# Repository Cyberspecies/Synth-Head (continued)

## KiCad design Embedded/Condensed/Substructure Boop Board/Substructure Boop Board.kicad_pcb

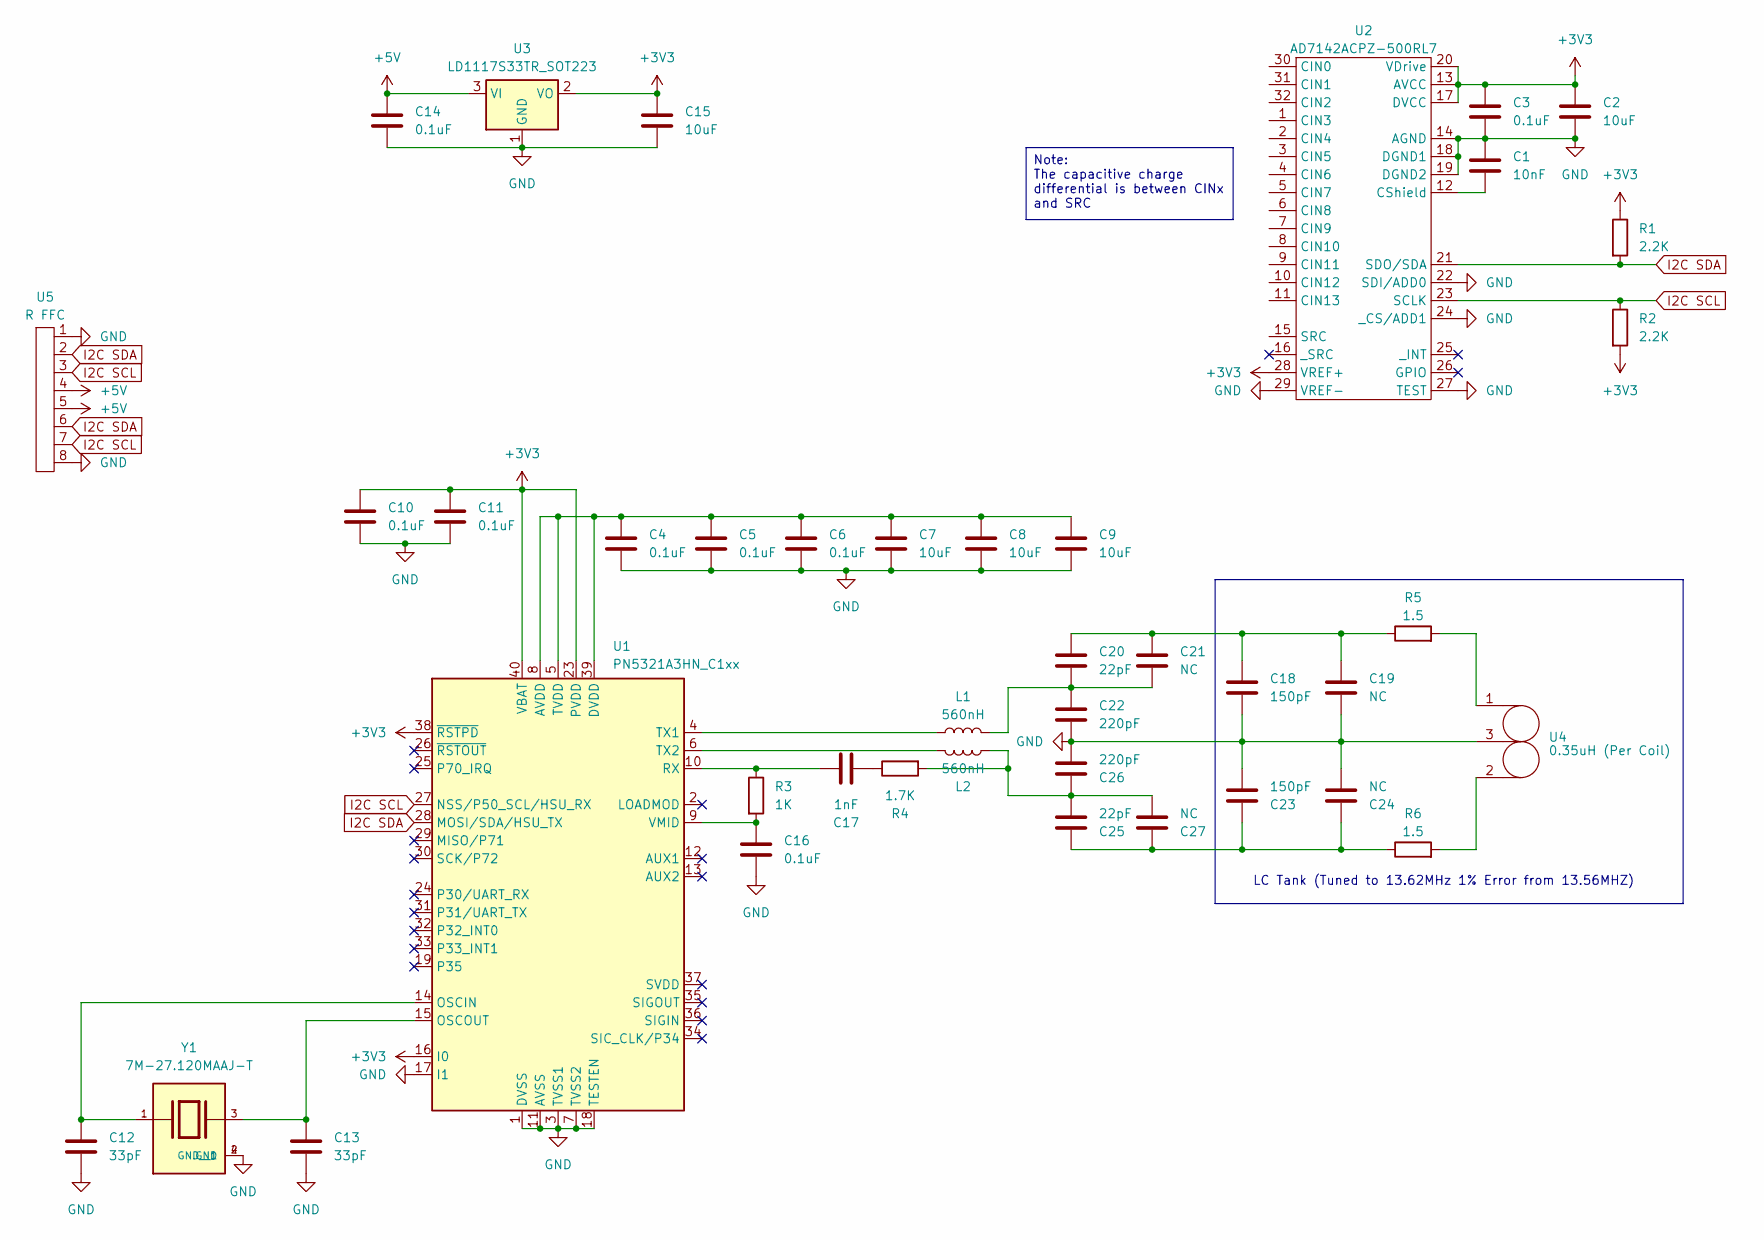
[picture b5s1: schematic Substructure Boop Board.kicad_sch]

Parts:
C1: 10nF; C_0402_1005Metric_Pad0.74x0.62mm_HandSolder; LCSC C327025
C2, C7, C8, C9: 10uF; C_0402_1005Metric_Pad0.74x0.62mm_HandSolder; LCSC C15525
C3, C4, C5, C6, C10, C11, C16: 0.1uF; C_0402_1005Metric_Pad0.74x0.62mm_HandSolder; LCSC C1525
C12, C13: 33pF; C_0402_1005Metric_Pad0.74x0.62mm_HandSolder; LCSC C70465
C14: 0.1uF; C_0603_1608Metric_Pad1.08x0.95mm_HandSolder; LCSC C1591
C15: 10uF; C_0603_1608Metric_Pad1.08x0.95mm_HandSolder; LCSC C3039698
C17: 1nF; C_0402_1005Metric_Pad0.74x0.62mm_HandSolder; LCSC C14442
C18, C23: 150pF; C_0402_1005Metric_Pad0.74x0.62mm_HandSolder; LCSC C86286
C19, C21, C24, C27: NC; C_0402_1005Metric_Pad0.74x0.62mm_HandSolder
C20, C25: 22pF; C_0402_1005Metric_Pad0.74x0.62mm_HandSolder; LCSC C307342
C22, C26: 220pF; C_0402_1005Metric_Pad0.74x0.62mm_HandSolder; LCSC C307445
L1, L2: 560nH; L_0603_1608Metric_Pad1.05x0.95mm_HandSolder; LCSC C502009
R1, R2: 2.2K; C_0402_1005Metric_Pad0.74x0.62mm_HandSolder; LCSC C163447
R3: 1K; C_0402_1005Metric_Pad0.74x0.62mm_HandSolder; LCSC C844716
R4: 1.7K; C_0402_1005Metric_Pad0.74x0.62mm_HandSolder; LCSC C482079
R5, R6: 1.5; C_0402_1005Metric_Pad0.74x0.62mm_HandSolder; LCSC C482091
U1: PN5321A3HN_C1xx; HVQFN-40-1EP_6x6mm_P0.5mm_EP4.1x4.1mm; LCSC C28925
U2: AD7142ACPZ-500RL7; LFCSP-32-1EP_5x5mm_P0.5mm_EP3.1x3.1mm_ThermalVias; LCSC C208139
U3: LD1117S33TR_SOT223; SOT-223-3_TabPin2; LCSC C86781
U4: 0.35uH (Per Coil); 30 x 40 - 2 Pair 2 Layer 2 Turn Loop Antenna
U5: R FFC; FFC 0.8mm 8P
Y1: 7M-27.120MAAJ-T; XTAL_7M-27.120MAAJ-T; PARTREV N/A; DIGIKEY 887-1424-1-ND

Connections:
+3V3: C2.1, C3.1, C10.1, C11.1, C15.1, R1.1, R2.2, U1.16 (I0), U1.23 (PVDD), U1.38 (~RSTPD), U1.40 (VBAT), U2.13 (AVCC), U2.17 (DVCC), U2.20 (VDrive), U2.28 (VREF+), U3.2 (VO)
+5V: C14.1, U3.3 (VI), U5.4, U5.5
GND: C1.1, C2.2, C3.2, C4.2, C5.2, C6.2, C7.2, C8.2, C9.2, C10.2, C11.2, C12.2, C13.2, C14.2, C15.2, C16.2, C18.2, C19.2, C22.2, C23.2, C24.2, C26.1, U1.1 (DVSS), U1.3 (TVSS1), U1.7 (TVSS2), U1.11 (AVSS), U1.17 (I1), U1.18 (TESTEN), U1.41 (AVSS), U2.14 (AGND), U2.18 (DGND1), U2.19 (DGND2), U2.22 (SDI/ADD0), U2.24 (_CS/ADD1), U2.27 (TEST), U2.29 (VREF-), U3.1 (GND), U4.3, U5.1, U5.8, Y1.2 (GND), Y1.4 (GND__1)
I2C SCL: R2.1, U1.27 (NSS/P50_SCL/HSU_RX), U2.23 (SCLK), U5.3, U5.7
I2C SDA: R1.2, U1.28 (MOSI/SDA/HSU_TX), U2.21 (SDO/SDA), U5.2, U5.6
unnamed: C17.2, R4.1
unnamed: C18.1, C19.1, C20.1, C21.1, R5.1
unnamed: C20.2, C21.2, C22.1, L1.2
unnamed: C23.1, C24.1, C25.1, C27.1, R6.1
unnamed: C25.2, C26.2, C27.2, L2.2, R4.2
unnamed: R5.2, U4.1
unnamed: R6.2, U4.2
unnamed: C4.1, C5.1, C6.1, C7.1, C8.1, C9.1, U1.5 (TVDD), U1.8 (AVDD), U1.39 (DVDD)
unnamed: C12.1, U1.14 (OSCIN), Y1.1
unnamed: C13.1, U1.15 (OSCOUT), Y1.3
unnamed: C17.1, R3.1, U1.10 (RX)
unnamed: L1.1, U1.4 (TX1)
unnamed: L2.1, U1.6 (TX2)
unnamed: C16.1, R3.2, U1.9 (VMID)
unnamed: C1.2, U2.12 (CShield)

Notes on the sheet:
LC Tank (Tuned to 13.62MHz 1% Error from 13.56MHZ)
Note: The capacitive charge differential is between CINx and SRC

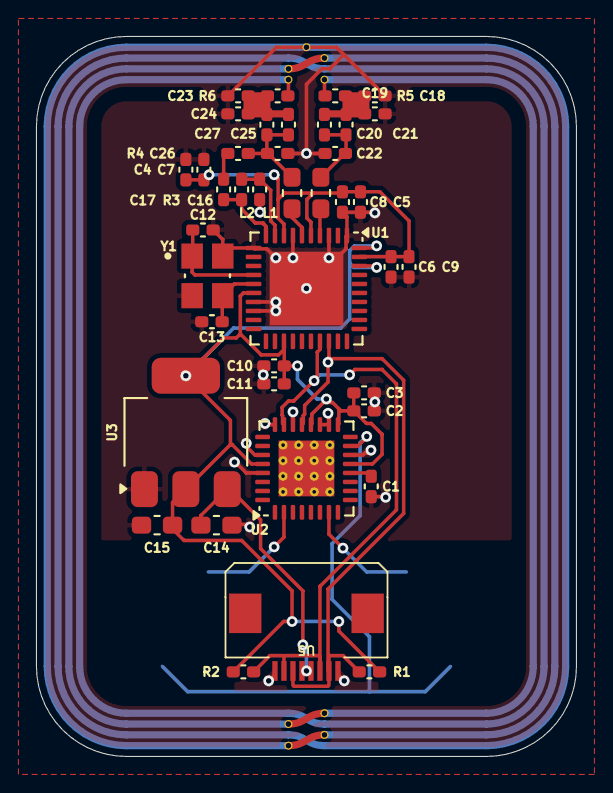
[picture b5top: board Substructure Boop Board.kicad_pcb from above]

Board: 2 copper layers, 30.0 x 40.0 mm, 41 parts (1 on the bottom side), 20 nets.

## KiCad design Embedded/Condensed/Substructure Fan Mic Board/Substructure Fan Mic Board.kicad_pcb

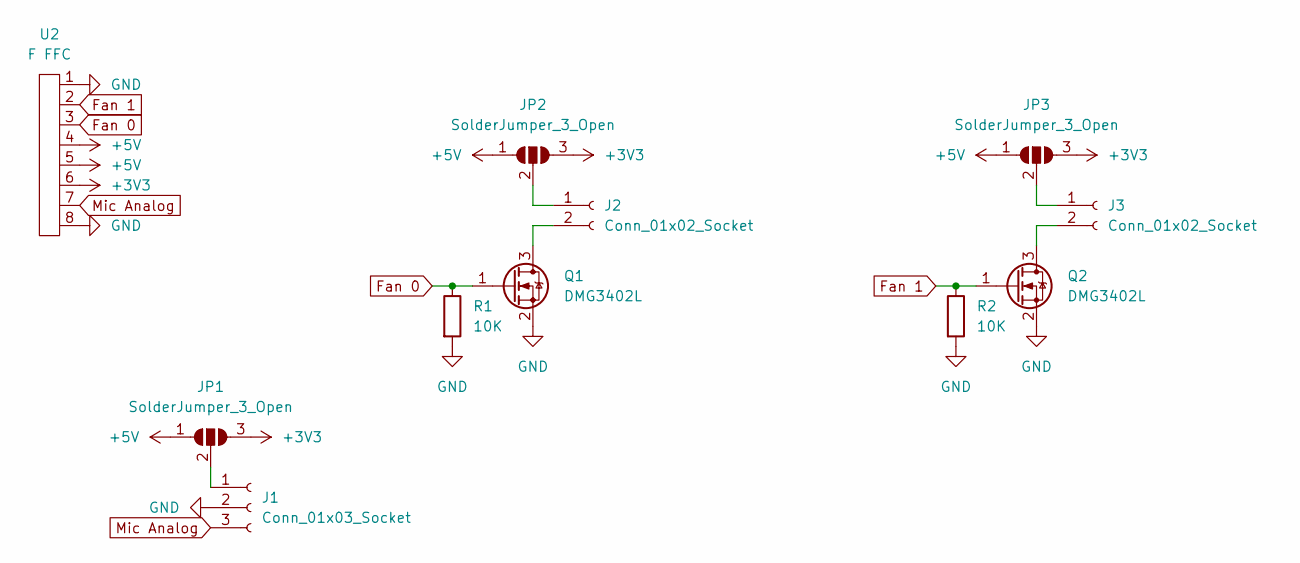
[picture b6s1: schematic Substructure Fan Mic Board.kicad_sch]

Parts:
J1: Conn_01x03_Socket; JST_GH_SM03B-GHS-TB_1x03-1MP_P1.25mm_Horizontal
J2, J3: Conn_01x02_Socket; JST_GH_SM02B-GHS-TB_1x02-1MP_P1.25mm_Horizontal
JP1, JP2, JP3: SolderJumper_3_Open; SolderJumper-3_P1.3mm_Open_RoundedPad1.0x1.5mm
Q1, Q2: DMG3402L; SOT-23; LCSC C96614
R1, R2: 10K; R_0603_1608Metric_Pad0.98x0.95mm_HandSolder; LCSC C98220
U2: F FFC; FFC 0.8mm 8P

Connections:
+3V3: JP1.3 (B), JP2.3 (B), JP3.3 (B), U2.6
+5V: JP1.1 (A), JP2.1 (A), JP3.1 (A), U2.4, U2.5
Fan 0: Q1.1 (G), R1.1, U2.3
Fan 1: Q2.1 (G), R2.1, U2.2
GND: J1.2, Q1.2 (S), Q2.2 (S), R1.2, R2.2, U2.1, U2.8
Mic Analog: J1.3, U2.7
unnamed: J1.1, JP1.2 (C)
unnamed: J2.1, JP2.2 (C)
unnamed: J2.2, Q1.3 (D)
unnamed: J3.1, JP3.2 (C)
unnamed: J3.2, Q2.3 (D)

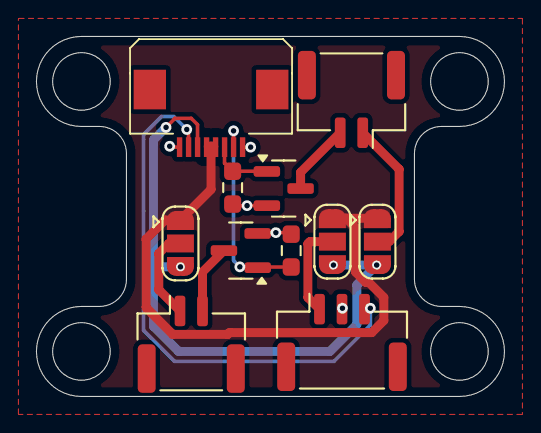
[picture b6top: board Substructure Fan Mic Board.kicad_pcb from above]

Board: 2 copper layers, 26.0 x 20.0 mm, 11 parts (0 on the bottom side), 11 nets.

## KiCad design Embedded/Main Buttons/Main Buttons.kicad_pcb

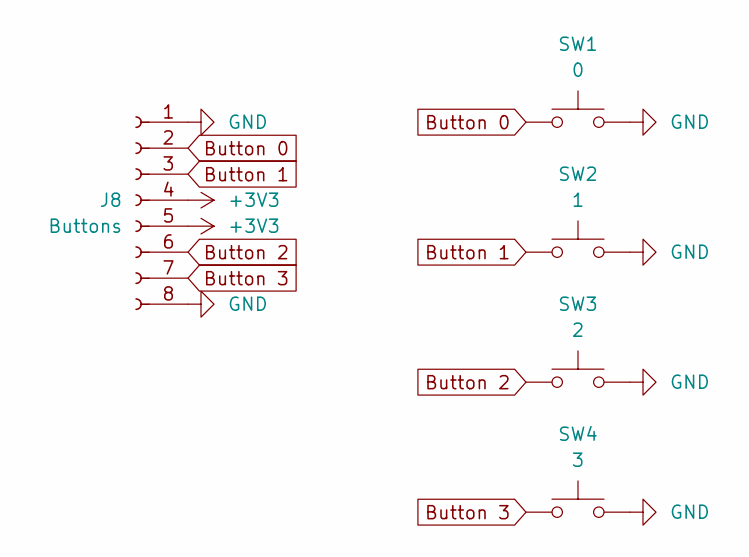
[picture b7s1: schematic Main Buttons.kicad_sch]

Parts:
J8: Buttons; JST_GH_SM08B-GHS-TB_1x08-1MP_P1.25mm_Horizontal
SW1: 0; SW_PUSH_6mm_H5mm
SW2: 1; SW_PUSH_6mm_H5mm
SW3: 2; SW_PUSH_6mm_H5mm
SW4: 3; SW_PUSH_6mm_H5mm

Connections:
+3V3: J8.4, J8.5
Button 0: J8.2, SW1.1
Button 1: J8.3, SW2.1
Button 2: J8.6, SW3.1
Button 3: J8.7, SW4.1
GND: J8.1, J8.8, SW1.2, SW2.2, SW3.2, SW4.2

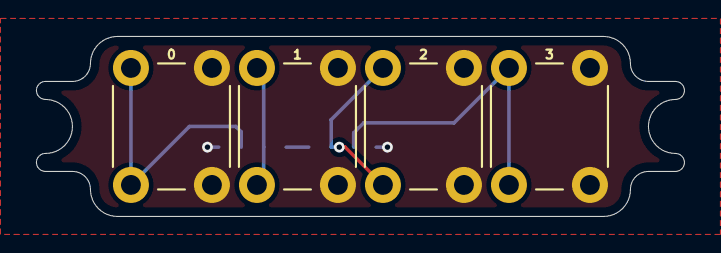
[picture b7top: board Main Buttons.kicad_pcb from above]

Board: 2 copper layers, 36.0 x 10.0 mm, 5 parts (1 on the bottom side), 6 nets.

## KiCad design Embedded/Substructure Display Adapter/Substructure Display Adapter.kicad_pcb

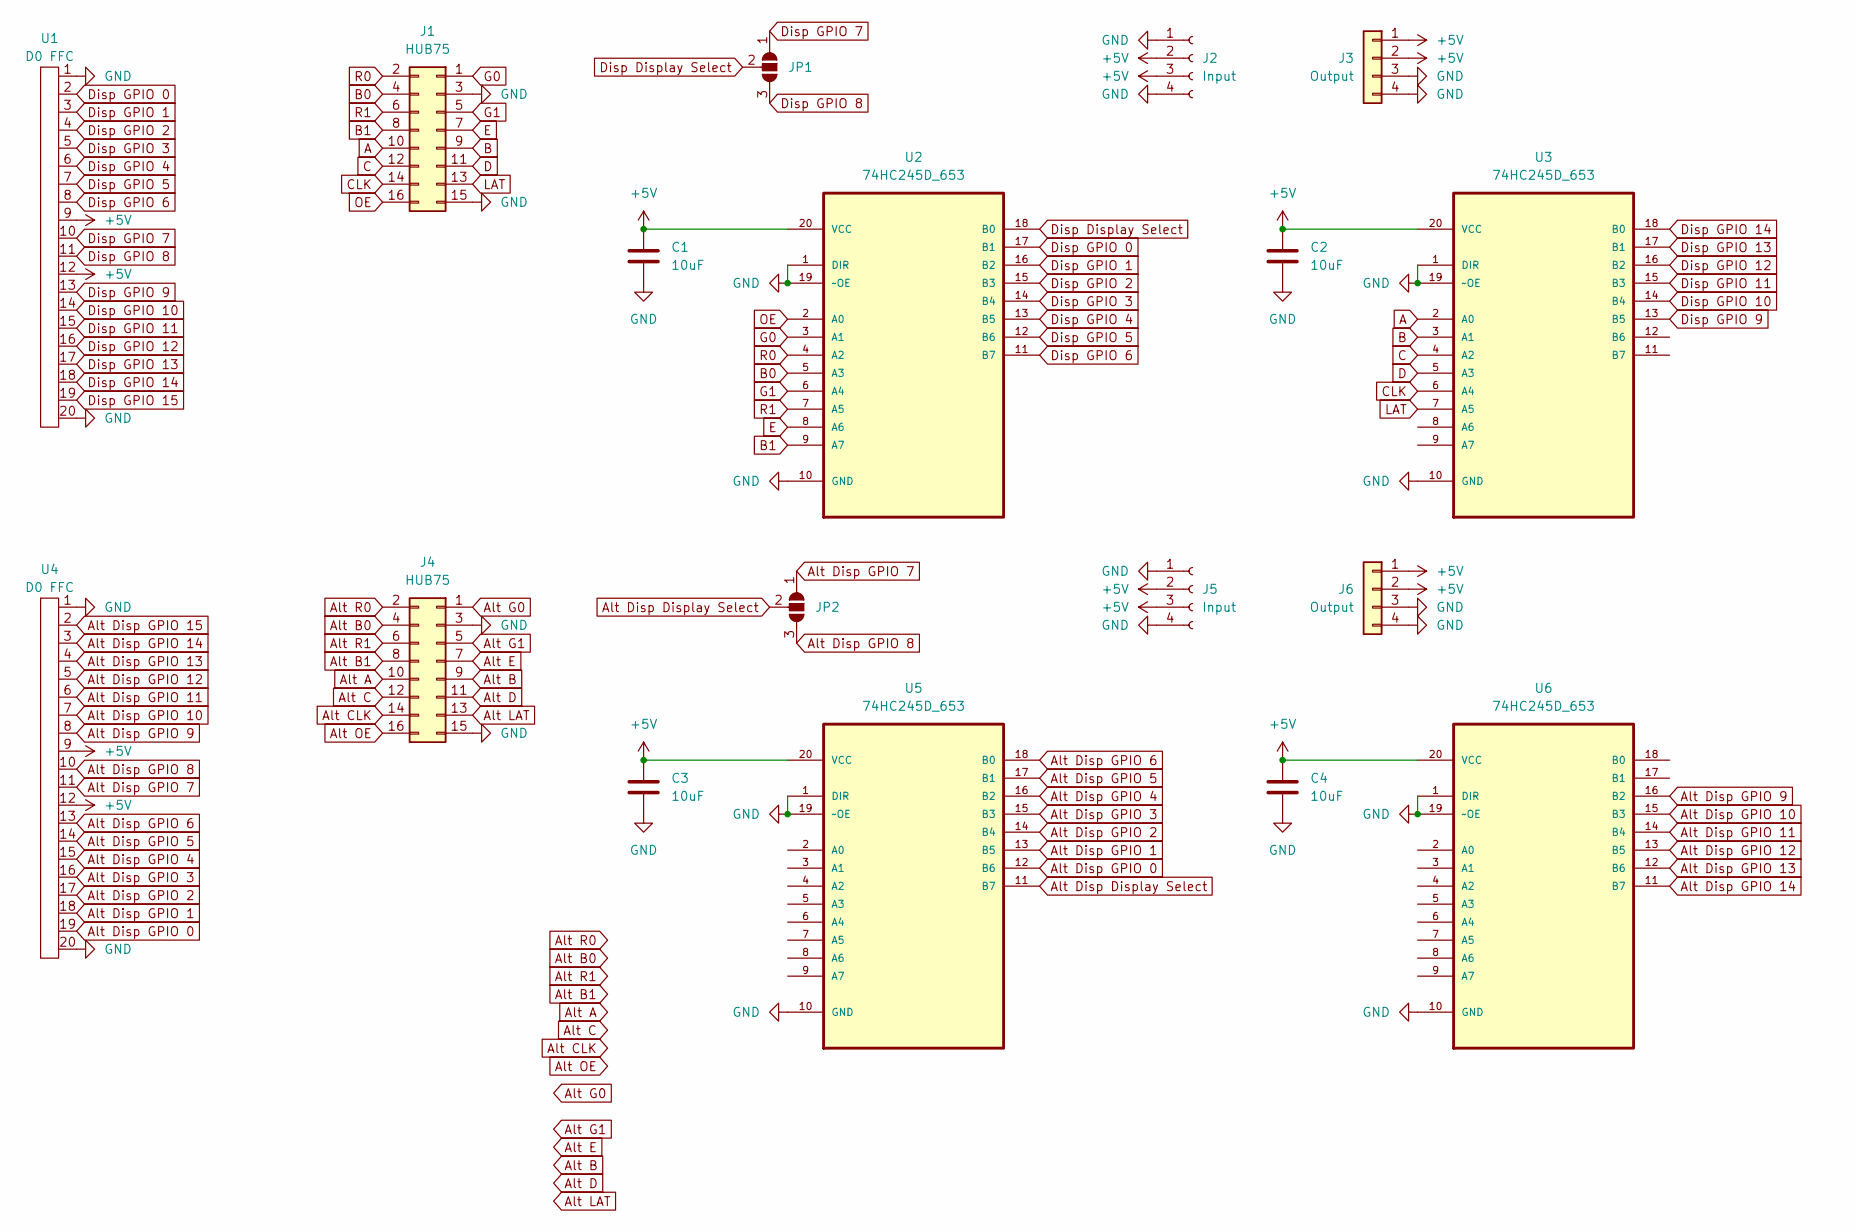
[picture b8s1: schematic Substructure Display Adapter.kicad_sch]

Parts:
C1, C2, C3, C4: 10uF; C_0603_1608Metric_Pad1.08x0.95mm_HandSolder; LCSC C95839
J1, J4: HUB75; PinHeader_2x08_P2.54mm_Vertical; LCSC C30734
J2, J5: Input; JST_XH_S4B-XH-A_1x04_P2.50mm_Horizontal
J3, J6: Output; JST_VH_B4P-VH-B_1x04_P3.96mm_Vertical
JP1, JP2: SolderJumper_3_Open; SolderJumper-3_P1.3mm_Open_RoundedPad1.0x1.5mm_NumberLabels
U1, U4: D0 FFC; FFC 0.8mm 20P
U2, U3, U5, U6: 74HC245D_653; SOIC127P1032X265-20N; MPN 74HC245D,653; LCSC C5625

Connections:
+5V: C1.1, C2.1, C3.1, C4.1, J2.2, J2.3, J3.1, J3.2, J5.2, J5.3, J6.1, J6.2, U1.9, U1.12, U2.20 (VCC), U3.20 (VCC), U4.9, U4.12, U5.20 (VCC), U6.20 (VCC)
A: J1.10, U3.2 (A0)
Alt A: J4.10, U5.4 (A2)
Alt B: J4.9, U5.3 (A1)
Alt B0: J4.4, U6.6 (A4)
Alt B1: J4.8, U5.2 (A0)
Alt C: J4.12, U5.6 (A4)
Alt CLK: J4.14, U5.8 (A6)
Alt D: J4.11, U5.5 (A3)
Alt Disp Display Select: JP2.2 (C), U5.11 (B7)
Alt Disp GPIO 0: U4.19, U5.12 (B6)
Alt Disp GPIO 1: U4.18, U5.13 (B5)
Alt Disp GPIO 2: U4.17, U5.14 (B4)
Alt Disp GPIO 3: U4.16, U5.15 (B3)
Alt Disp GPIO 4: U4.15, U5.16 (B2)
Alt Disp GPIO 5: U4.14, U5.17 (B1)
Alt Disp GPIO 6: U4.13, U5.18 (B0)
Alt Disp GPIO 7: JP2.1 (A), U4.11
Alt Disp GPIO 8: JP2.3 (B), U4.10
Alt Disp GPIO 9: U4.8, U6.16 (B2)
Alt Disp GPIO 10: U4.7, U6.15 (B3)
Alt Disp GPIO 11: U4.6, U6.14 (B4)
Alt Disp GPIO 12: U4.5, U6.13 (B5)
Alt Disp GPIO 13: U4.4, U6.12 (B6)
Alt Disp GPIO 14: U4.3, U6.11 (B7)
Alt Disp GPIO 15: U4.2
Alt E: J4.7, U6.9 (A7)
Alt G0: J4.1, U6.4 (A2)
Alt G1: J4.5, U6.7 (A5)
Alt LAT: J4.13, U5.7 (A5)
Alt OE: J4.16, U5.9 (A7)
Alt R0: J4.2, U6.5 (A3)
Alt R1: J4.6, U6.8 (A6)
B: J1.9, U3.3 (A1)
B0: J1.4, U2.5 (A3)
B1: J1.8, U2.9 (A7)
C: J1.12, U3.4 (A2)
CLK: J1.14, U3.6 (A4)
D: J1.11, U3.5 (A3)
Disp Display Select: JP1.2 (C), U2.18 (B0)
Disp GPIO 0: U1.2, U2.17 (B1)
Disp GPIO 1: U1.3, U2.16 (B2)
Disp GPIO 2: U1.4, U2.15 (B3)
Disp GPIO 3: U1.5, U2.14 (B4)
Disp GPIO 4: U1.6, U2.13 (B5)
Disp GPIO 5: U1.7, U2.12 (B6)
Disp GPIO 6: U1.8, U2.11 (B7)
Disp GPIO 7: JP1.1 (A), U1.10
Disp GPIO 8: JP1.3 (B), U1.11
Disp GPIO 9: U1.13, U3.13 (B5)
Disp GPIO 10: U1.14, U3.14 (B4)
Disp GPIO 11: U1.15, U3.15 (B3)
Disp GPIO 12: U1.16, U3.16 (B2)
Disp GPIO 13: U1.17, U3.17 (B1)
Disp GPIO 14: U1.18, U3.18 (B0)
Disp GPIO 15: U1.19
E: J1.7, U2.8 (A6)
G0: J1.1, U2.3 (A1)
G1: J1.5, U2.6 (A4)
GND: C1.2, C2.2, C3.2, C4.2, J1.3, J1.15, J2.1, J2.4, J3.3, J3.4, J4.3, J4.15, J5.1, J5.4, J6.3, J6.4, U1.1, U1.20, U2.1 (DIR), U2.10 (GND), U2.19 (~OE), U3.1 (DIR), U3.10 (GND), U3.19 (~OE), U4.1, U4.20, U5.1 (DIR), U5.10 (GND), U5.19 (~OE), U6.1 (DIR), U6.10 (GND), U6.19 (~OE)
LAT: J1.13, U3.7 (A5)
OE: J1.16, U2.2 (A0)
R0: J1.2, U2.4 (A2)
R1: J1.6, U2.7 (A5)

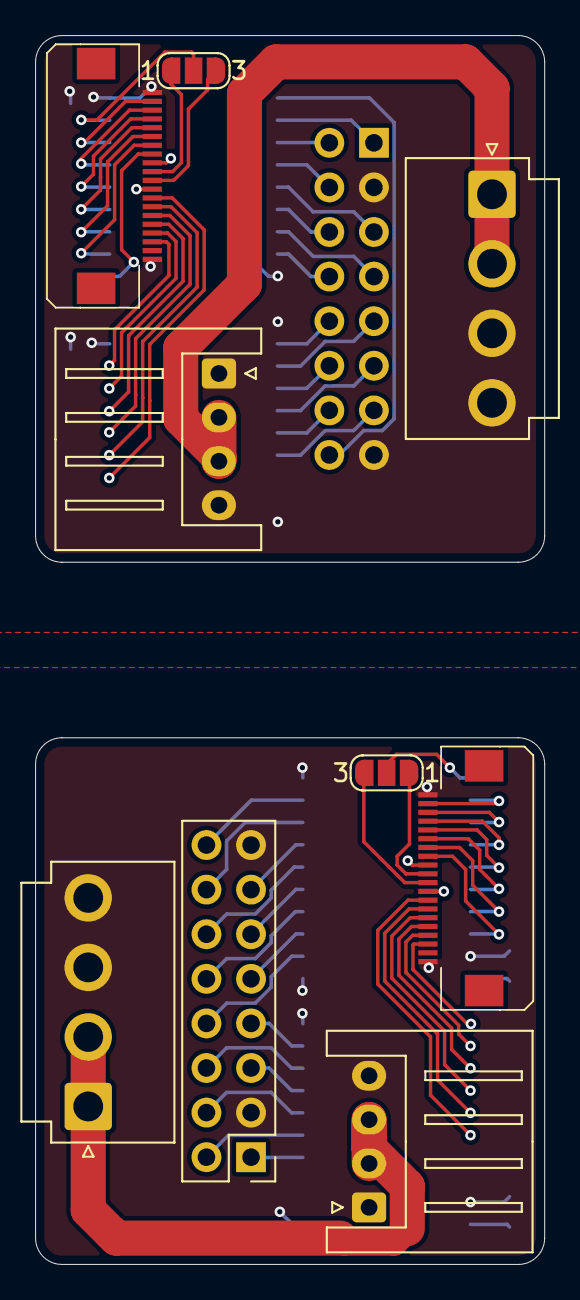
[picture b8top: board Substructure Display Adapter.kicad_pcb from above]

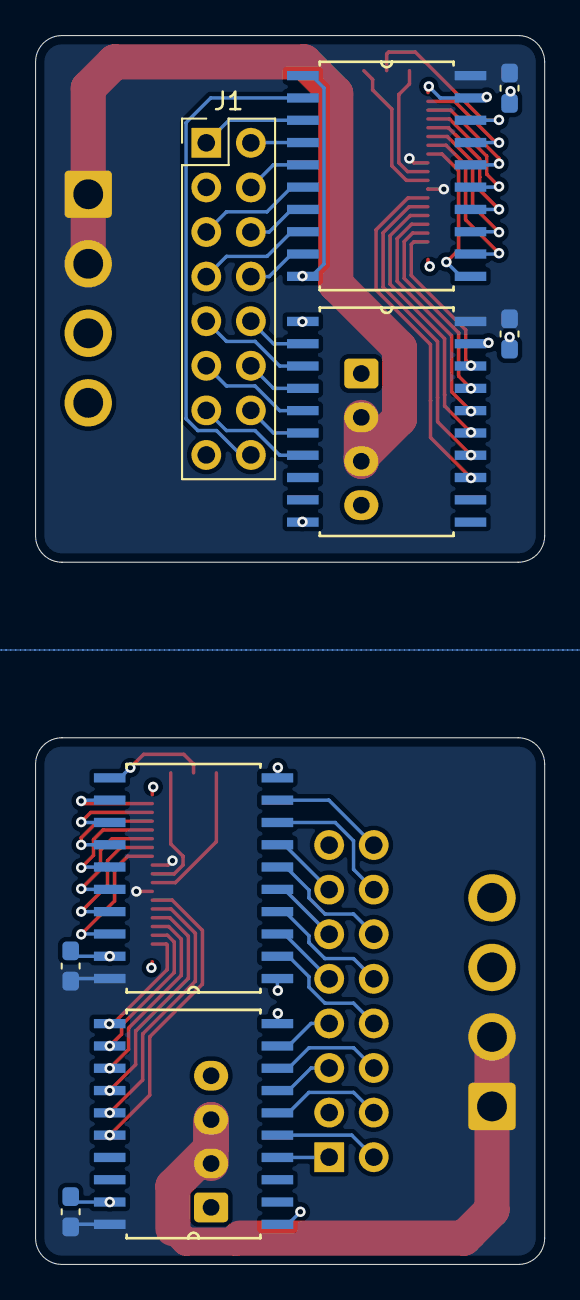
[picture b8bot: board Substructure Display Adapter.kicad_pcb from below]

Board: 2 copper layers, 29.0 x 70.0 mm, 18 parts (9 on the bottom side), 62 nets.

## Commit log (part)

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2025-07-07 Added Pin Assignments & Signal Routing
2025-07-07 Added Minimum Safety Circuit
2025-07-08 Added ESD diode selection
2025-07-09 Added Simple crowbar circuit
2025-07-10 Added Window comparator component selection
2025-07-11 Added P Channel mosfets & crow bar circuits
2025-07-11 Modified Safety Circuit (Removed Windowed Comparator)
2025-07-11 Added Component footprints
2025-07-11 Added Component Placement
2025-07-12 Added Buck converter driver routing
2025-07-13 Added FFC Port Direction Diagrams
2025-07-13 Modified Ports to fit FFC orientations
2025-07-14 Added Mounting Holes
2025-07-15 Added Synapse protocal standard
2025-07-16 Added Component placement ideation
2025-07-16 Added DX.4 (Recondensed) Diagram for production ready design
2025-07-16 Added Routing for right adapter
2025-07-17 Modified Fill plane to detach each pcb from each other
2025-07-17 Added SMT Batch for 4 Layer PCBs
2025-07-18 Added Recondensed system for simplicity whilst maintaining core functions
2025-07-18 Added Footprints to components
2025-07-18 Added Component groupings
2025-07-18 Added Component placement positions
2025-07-20 Added Routing for all pins and pads
2025-07-20 Added Component placement for main systems
2025-07-21 Added Component placement for driver components
2025-07-21 Added GPU Routing
2025-07-21 Added New Routing (Improved board space & signal noise)
2025-07-22 Added Substructure to Main Adapter
2025-07-23 Modified Addressable LED strip labels for general systems
2025-07-23 Modified Addressable LED ports for general (instead of static config names)
2025-07-24 Added More structural elements & cable management
2025-07-25 Added Linkage Ideation
2025-07-25 Modified Display pins (Corrected port orientation) & Added Silkscreen Data
2025-07-25 Modified UART Pins & Added Silkscreen Data
2025-07-25 Modified Buttons from pull down to pull up
2025-07-26 Modified Folder structure (Migrated files)
2025-07-26 Updated Asset Dates
2025-07-27 Added 4 Layer Batch
2025-07-27 Added JLCPCB Production Files
2025-07-27 Modified Folder Structure (Moved production files)
2025-07-27 Modified Batch to be Production Ready
2025-07-29 Added Hardware Fixes (New Magnetic Jaw Joint Ideation)
2025-07-30 Added List of Hardware Parts to Upgrade
2025-07-31 Added Communication purpose/description
2025-07-31 Added 4 Bar linkage mounting ideation
2025-08-02 Added Main Board Placements
2025-08-03 Added Jaw Joint Position Ideation
2025-08-03 Added (.kra~) to ignore
2025-08-03 Modified File for hardware upgrades & positioning
2025-08-04 Added Main CAD Files
2025-08-04 Added Mask
2025-08-04 Added 4 Bar Linkage Mechanism (Prototype)
2025-08-05 Modified 4 Bar Linkage (Improved Mounting Plate)
2025-08-05 Added Head Retention Mechanism
2025-08-07 Added SD Card Checker
    Checks SD Card that is plugged in and allows you to choose and open the files along with displaying its metadata
2025-08-07 Added Simple HUB75 Driver
    Very basic driver to test the HUB75 pins
2025-08-07 Modified Drawing (Redrew optimised layout)
2025-08-08 Added Separated Cable & Neck Plates Idea
2025-08-08 Added Compression Articulation for Scales & Tensioning Idea
2025-08-08 Added Electronics Cover
2025-08-09 Added Simple clip based battery mount
2025-08-09 Added Cable attachment mechanism for scales
2025-08-10 Added Head front restraint
2025-08-10 Added Shape ideation for the substructure
2025-08-12 Added Substructure & Display Panel Mounting
2025-08-12 Added Front scales & mounting
2025-08-13 Added Main to substructure pogo pin connector port
2025-08-14 Added Side vent air flow guides
2025-08-14 Added Required Orders
2025-08-14 Added Interface boards & components section
2025-08-15 Added simple working dual panel tester (has issues but works)
2025-08-16 Modified Mask to be removable & top maw plate
2025-08-20 Added Jaw ventilation port
2025-08-20 Added Buttons
2025-08-21 Added INMP441 mount
2025-08-21 Added Panel Antenna (Placeholder 42mm x 12mm x 0.3mm)
2025-08-22 Added Alternative cable & plate mounting
2025-08-25 Added Front scale to scale linkage mechanism
2025-08-25 Added Back scale magnetic connector to main
2025-08-25 Added Sliding snap fit front to back scales attachment mechanism
2025-08-26 Added Back scale addressable LED strip inlay groove
2025-08-28 Added Main board routing estimation
2025-08-28 Added HUD blank mount
2025-08-29 Added Display Layout
2025-08-30 Added Main to attached scale (cable guide)
2025-08-30 Added Scale to Scale cable guides for LEDs
2025-08-31 Added Jaw cable guide grooves & cable hole
2025-09-01 Added Substructure cable groove
2025-09-01 Added OLED display adapter
2025-09-03 Added Cable requirement and orientation diagram
2025-09-06 Added Wroom32 hole to substructure (fitting issues)
2025-09-13 Added Reinforcements to CPU mount tabs
2025-09-23 Added Software Diagram (Core purpose allocation)
2025-09-24 Added Nav orb
2025-09-24 Added More components
2025-09-24 Added Bottom temporary mount for welding (Jaw)
2025-09-26 Modified Jaw Joint (Spun joining mechanism 180deg around to allow the jaw to lock into place)
2025-09-27 Modified Values
2025-09-27 Added Reduced version features and fabricator requirements
2025-09-28 Added Hardware architecture ideation
2025-09-28 Added Alpha release software stack (CPU)
2025-09-28 Added Data sent between the CPU and the GPU
2025-09-28 Modified Weld mounts to be square rather than single
2025-09-28 Modified Rubber band mounts to have cut outs (easier to insert rubber bands)
2025-09-28 Added Foam slots and adhesive channels
2025-09-29 Modified Fin Feature Insert (filleted cable slots) to improve support generation
2025-09-29 Modified File to include vacuum buck (forgot to add it in previous commits)
2025-10-08 Added SD management
2025-10-08 Added Alpha release software testing with hybrid external libraries
2025-10-10 Added New times accounting for new printing system
2025-10-13 Modified Vacuum buck to account for shrinkage
2025-10-13 Added Notes
2025-10-14 Added More optimisation notes
2025-10-14 Added More notes (Embedded & Electrical Heavy)
2025-10-15 Added CPU Pin mapping and feature mapping
2025-10-15 Modified Main Black print plastic usage
2025-10-15 Added More Hardware notes for vacuum forming & cable routing
2025-10-16 Added Visor Buck
2025-10-16 Added Mass & Time for visor buck (ASA)
2025-10-17 Modified File structure to be espidf compatible (removed spaces in address)
2025-10-18 Added Testing files
2025-10-19 Added Feature Ideas
2025-10-20 Added More notes regarding hardware and rubber band mounting
2025-10-21 Added Hardware pogo pins disconnecting due to flexing issue to notes
2025-10-22 Modified Substructure port position to account for mounting tolerance
2025-10-23 Added Boot, Idle & Shutdown faces
2025-10-24 Added Button configurations
2025-10-24 Added Simple folder structure
2025-10-24 Added Battery mount
2025-10-26 Added Vacuum forming process brainstorming diagram
2025-10-27 Added PETG test process to diagram
2025-10-27 Added Vacuum forming buck notes about drafts
2025-10-27 Added New visor buck design with significantly reduced underdrafts
2025-10-27 Added Electronics cover to notes
2025-10-30 Added Further petg specifications on vacuum forming
2025-11-01 Added More vacuum forming notes (more machine specifics)
2025-11-01 Added Compatibility system to vacuum forming process
2025-11-05 Added Current issues to diagram
2025-11-05 Modified Issues analysis to use pseudo venn diagram
2025-11-06 Added Successful working systems
2025-11-07 Added Issues and troubleshooting with the dyeing process
2025-11-08 Added Simple GPU Systm
2025-11-08 Added UART Protocal & established bidirectional communication
2025-11-09 Added CPU & GPU Bidirectional up/down links at high throughput
2025-11-10 Modified UART communication analysis report (Fixed FPS bottleneck issue & reliablility calculations)
2025-11-11 Added Sensor data sent via UART from CPU to GPU
2025-11-11 Added HUB75 display support to system example
2025-11-11 Modified File structure to organise src folder
2025-11-11 Added Fan PWM control support
2025-11-12 Modified Entire file (properly calculating production)
2025-11-12 Added Menu system along with OLED to Display control
2025-11-13 Modified Website visuals and fixed corrupted icons
2025-11-14 Added The process down time issue to notes
2025-11-14 Modified File transfer protocol to allow proper images
2025-11-14 Added Easier web control system
2025-11-14 Added Bug fix for display size images not being sent & auto scaling for larger images than the buffer
2025-11-16 Added Animation support to HUB75 Display
2025-11-17 Added Surface finish and print setting notes
2025-11-18 Added More spray painting process notes based on experimentation
2025-11-18 Added Notes about clear coating
2025-11-19 Added Software notes on program structure
2025-12-02 Added Uart Test
2025-12-02 Added New software system architecture
2025-12-04 Added Print Recommendations
2025-12-04 Added Main white components
2025-12-05 Modified 4 Bar linkage (Reinforced the first joint & corrected tolerance for a tighter joint
2025-12-06 Added Fin feat holders and lever
2025-12-11 Added Notes for vacuum forming and visor dyeing
2025-12-23 Removed Obsolete pages
2025-12-31 Added CPU to GPU Frame buffer
2025-12-31 Added Frame request system for stable frame rate
2026-01-03 Added Pixel weight rasterisation & Added Bug fix (UART buffer overload)
2026-01-03 Added Splash screen and no signal screens
2026-01-04 Added Notes about no press fit electronics through THT mounting holes
2026-01-06 Added Minimal demo CPU code
2026-01-06 Modified Animation to static
2026-01-09 Added System lifecycle management
2026-01-09 Added Debug console based testing & Modified SystemTest to initialise on boot with A-D button hold
2026-01-10 Modified API
2026-01-13 Added Captive portal and web settings
2026-01-14 Added Ping Pong check and query gpu configuration and gpu status
2026-01-14 Added Equation manager
2026-01-14 Added MicroSD card storage
2026-01-16 Added Fix for GPU bug
    Fix was for sprites not being anti aliased which also prevented sprite rotation due to pixel math being wrong
2026-01-19 Added Sensor driver separation & Added Wifi sprite system test & Added GPU sprite driver & Added Pipeline fix for sprite to GPU in main CPU code
2026-01-19 Added Fix to directory names (Previously inconsistent capitalisation)
2026-01-20 Removed Starting image
2026-01-20 Added Glitch row offset effect
2026-01-20 Added Faster SDF algorithm using scanline
2026-01-20 Removed Obsolete systems
2026-01-21 Added LED Driver Support
2026-01-21 Added LED RGBW driver (using multiplexed RMT TX system)
2026-01-24 Added New OLED Display pages
2026-01-26 Modified Main with the new scene composer
2026-01-26 Added OLED Display handler integration
2026-01-27 Modified OLED from main run code (separated code) & Added Sensor bootloader fixes
2026-01-27 Added Auto scroll UI fix with long text
2026-01-27 Added Display replication for OLED
2026-01-29 Added Viewport ideation
2026-01-29 Added Removed bugs from YAML scene management
    - Not saving issue
    - Not applying effects issue
    - Many UI issues with auto generation of variables
2026-01-30 Added Display mirroring, panel orientation and panel order misalignment bug fix
2026-01-31 Added Panel ghosting fix
2026-01-31 Added Panel flashing and OLED delayed update fix
2026-01-31 Added New Dashboard next scene selector preview ideation
2026-02-01 Added Gradient cycling shader with angle control
2026-02-01 Added Glitch shader
2026-02-01 Added Scene not fully saving with all shaders bug fix
2026-02-01 Added OLED dashboard not displaying preview name bug fix
2026-02-02 Added LED Support
2026-02-02 Added Bug fix for SD disk erase function
2026-02-02 Added Recursively wiping SPIFFS system
2026-02-02 Added Reactive eyes animation type
2026-02-04 Added Sprites stuck in RAM bug fix
2026-02-04 Added Colour override not working bug fix
2026-02-04 Added GPS Time to viewport
2026-02-04 Added Mic support
